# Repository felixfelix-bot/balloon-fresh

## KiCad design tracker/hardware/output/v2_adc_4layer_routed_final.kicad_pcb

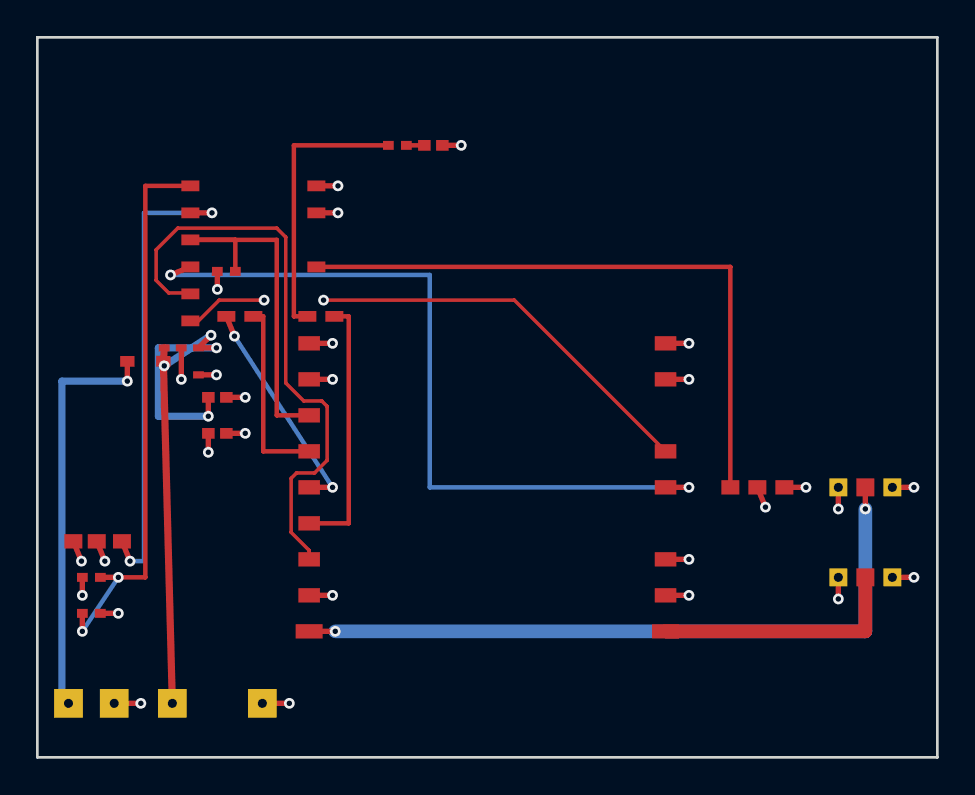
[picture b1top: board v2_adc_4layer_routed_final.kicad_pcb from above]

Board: 4 copper layers, 50.0 x 40.0 mm, 17 parts (0 on the bottom side), 18 nets.

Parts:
ANT1: U.FL-868
ANT2: U.FL-2400
C1, C2: 10uF
C_CAP: Supercap
D1: BAT54
FEM: FEM
LED1: LED-0603
R_DIV1, R_DIV2: 100k
R_LED: 330R
R_PD: 10k
SOLAR: Solar-Conn
U1: ESP32-C3
U2: LR2021F33
U3: MAX-M10S
U4: TPS7A02

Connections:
3V3: C2.1, FEM.VCC, R_DIV1.1, U1.VCC, U2.1, U3.1, U4.4
FEM_TX: FEM.TX, U1.GPIO19
GND: ANT1.2, ANT1.3, ANT2.2, ANT2.3, C1.2, C2.2, C_CAP.2, FEM.GND, LED1.K, R_DIV2.2, R_PD.1, SOLAR.2, U1.GND, U2.2, U2.8, U2.10, U2.11, U2.16, U2.17, U3.2, U4.2
GPS_RX: U1.GPIO1, U3.3
LED_ANODE: LED1.A, R_LED.2
LR2021_BUSY: U1.GPIO4, U2.7
LR2021_DIO9: U1.GPIO5, U2.13
LR2021_RST: U1.GPIO3, U2.14
RF_2G4_2400: ANT2.1, U2.18
RF_SUB_868: ANT1.1, U2.9
SOLAR_IN: D1.A, SOLAR.1
SPI_MISO: R_PD.2, U1.GPIO2, U2.3
SPI_MOSI: U1.GPIO7, U2.4
SPI_NSS: U1.GPIO10, U2.6
SPI_SCK: U1.GPIO6, U2.5
STATUS_LED: R_LED.1, U1.GPIO9
VCAP: C1.1, C_CAP.1, D1.K, U4.1, U4.3
VDIV_MID: R_DIV1.2, R_DIV2.1, U1.GPIO0
